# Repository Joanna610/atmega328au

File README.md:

# atmega328au

The project consist basic design of microcontroller avr atmega328.

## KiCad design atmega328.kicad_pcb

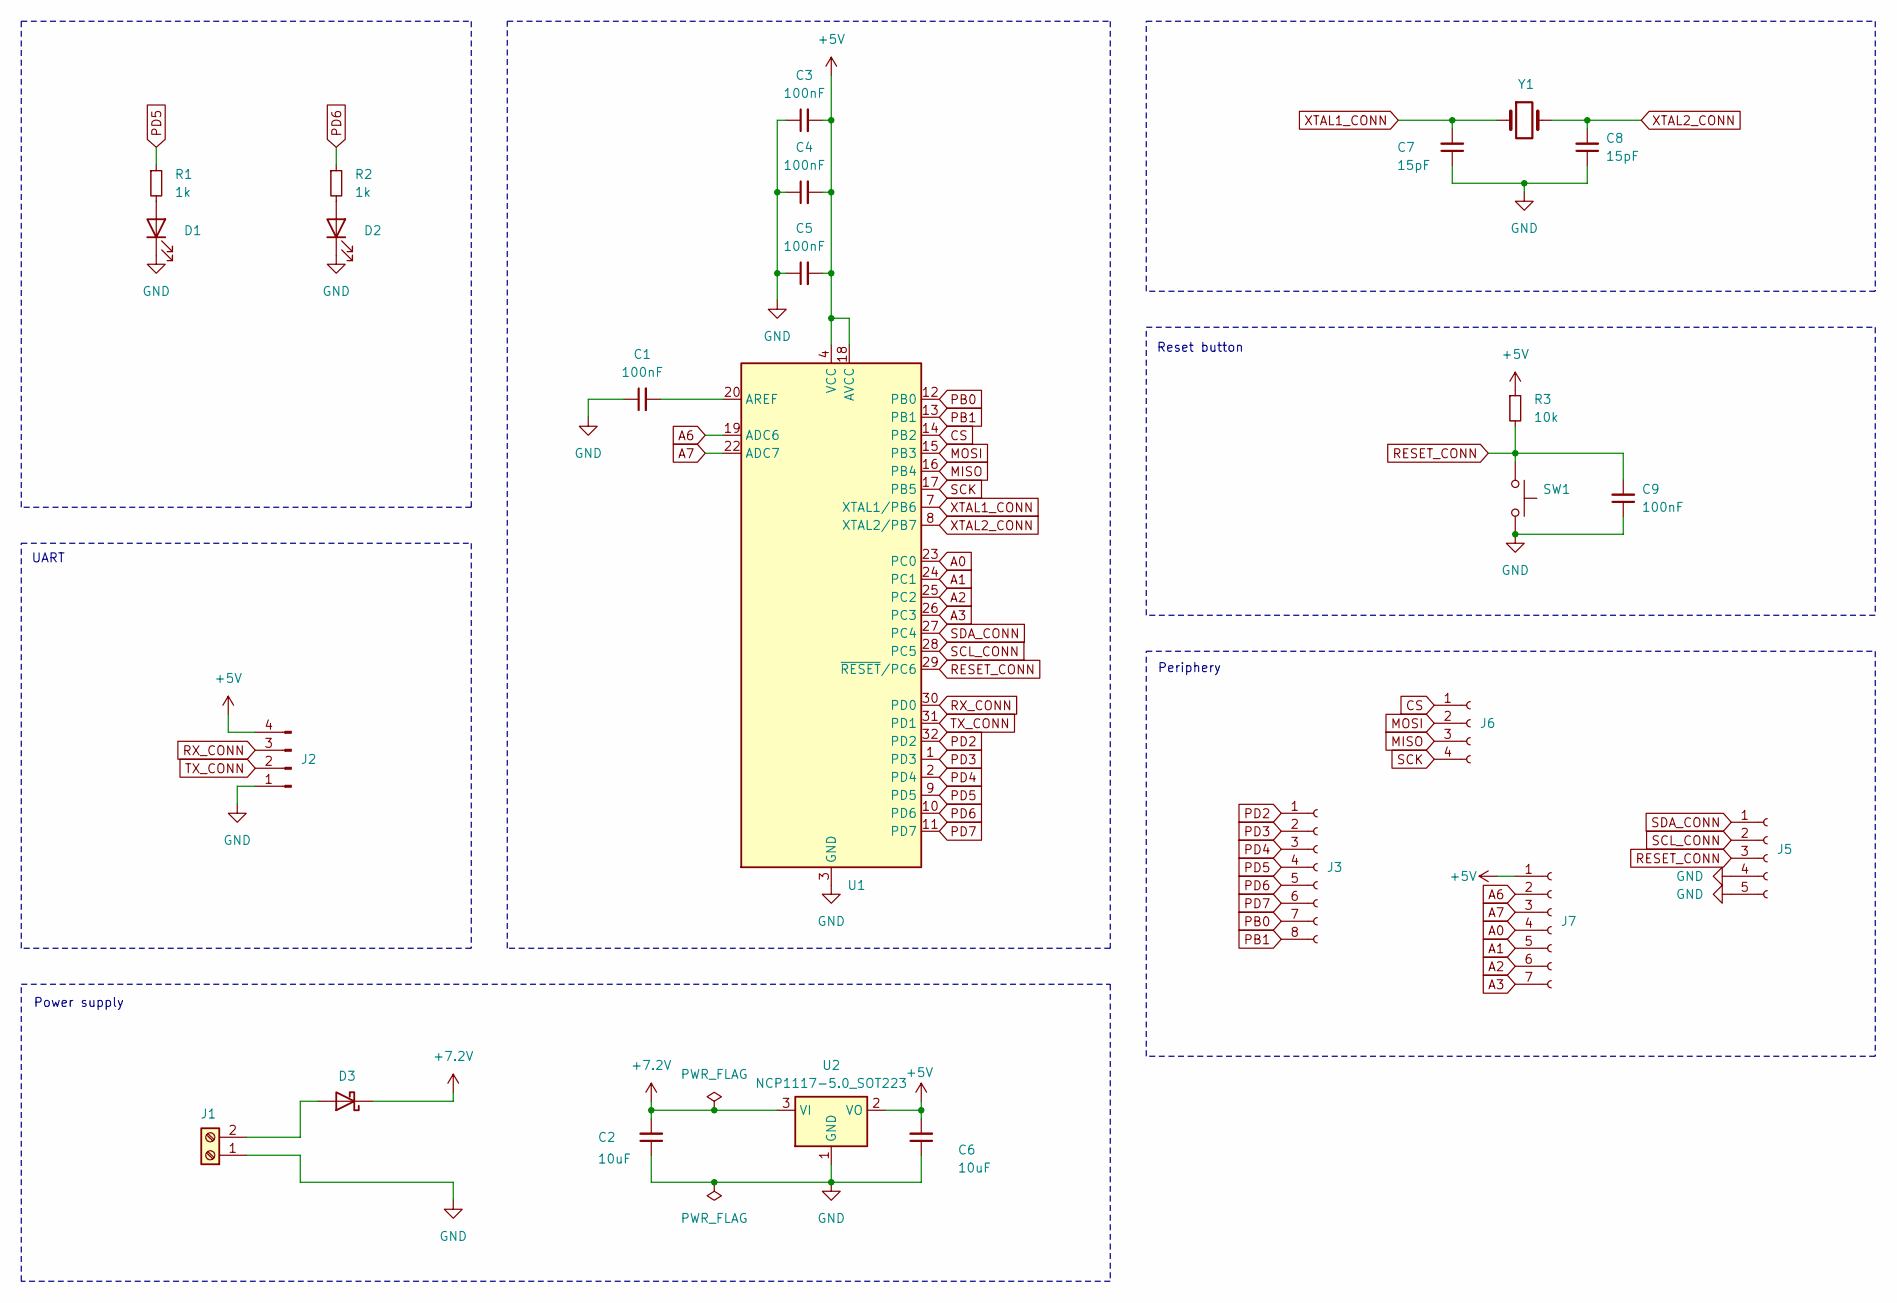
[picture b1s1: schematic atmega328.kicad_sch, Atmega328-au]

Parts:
C1, C3, C4, C5, C9: 100nF; C_0805_2012Metric_Pad1.18x1.45mm_HandSolder
C2, C6: 10uF; C_0805_2012Metric_Pad1.18x1.45mm_HandSolder
C7, C8: 15pF; C_0805_2012Metric_Pad1.18x1.45mm_HandSolder
D1, D2: LED; LED_1206_3216Metric_Pad1.42x1.75mm_HandSolder
D3: D_Schottky; R_Axial_DIN0207_L6.3mm_D2.5mm_P7.62mm_Horizontal
J1: input_supply; TE_826576-2_1x02_P3.96mm_Vertical
J2: UART; PinHeader_1x04_P2.54mm_Vertical
J3: Conn_01x08_Socket; PinSocket_1x08_P2.54mm_Vertical
J5: Conn_01x05_Socket; PinSocket_1x05_P2.54mm_Vertical
J6: Conn_01x04_Socket; PinSocket_1x04_P2.54mm_Vertical
J7: Conn_01x07_Socket; PinSocket_1x07_P2.54mm_Vertical
R1, R2: 1k; R_0805_2012Metric_Pad1.20x1.40mm_HandSolder
R3: 10k; R_0805_2012Metric_Pad1.20x1.40mm_HandSolder
SW1: SW_Push; SW_PUSH_1P1T_6x3.5mm_H5.0_APEM_MJTP1250
U1: ATmega328P-A; TQFP-32_7x7mm_P0.8mm
U2: NCP1117-5.0_SOT223; SOT-223-3_TabPin2
Y1: Crystal; Crystal_HC49-4H_Vertical

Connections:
+5V: C3.2, C4.2, C5.2, C6.2, J2.4, J7.1, R3.1, U1.4 (VCC), U1.6 (VCC), U1.18 (AVCC), U2.2 (VO)
+7.2V: C2.2, D3.1 (K), U2.3 (VI)
A0: J7.4, U1.23 (PC0)
A1: J7.5, U1.24 (PC1)
A2: J7.6, U1.25 (PC2)
A3: J7.7, U1.26 (PC3)
A6: J7.2, U1.19 (ADC6)
A7: J7.3, U1.22 (ADC7)
CS: J6.1, U1.14 (PB2)
GND: C1.1, C2.1, C3.1, C4.1, C5.1, C6.1, C7.1, C8.1, C9.1, D1.1 (K), D2.1 (K), J1.1, J2.1, J5.4, J5.5, SW1.2, U1.3 (GND), U1.5 (GND), U1.21 (GND), U2.1 (GND)
MISO: J6.3, U1.16 (PB4)
MOSI: J6.2, U1.15 (PB3)
unnamed: D1.2 (A), R1.2
unnamed: D2.2 (A), R2.2
unnamed: D3.2 (A), J1.2
unnamed: C1.2, U1.20 (AREF)
PB0: J3.7, U1.12 (PB0)
PB1: J3.8, U1.13 (PB1)
PD2: J3.1, U1.32 (PD2)
PD3: J3.2, U1.1 (PD3)
PD4: J3.3, U1.2 (PD4)
PD5: J3.4, R1.1, U1.9 (PD5)
PD6: J3.5, R2.1, U1.10 (PD6)
PD7: J3.6, U1.11 (PD7)
RESET_CONN: C9.2, J5.3, R3.2, SW1.1, U1.29 (~RESET/PC6)
RX_CONN: J2.3, U1.30 (PD0)
SCK: J6.4, U1.17 (PB5)
SCL_CONN: J5.2, U1.28 (PC5)
SDA_CONN: J5.1, U1.27 (PC4)
TX_CONN: J2.2, U1.31 (PD1)
XTAL1_CONN: C7.2, U1.7 (XTAL1/PB6), Y1.1
XTAL2_CONN: C8.2, U1.8 (XTAL2/PB7), Y1.2

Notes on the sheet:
Power supply
UART
Periphery
Reset button

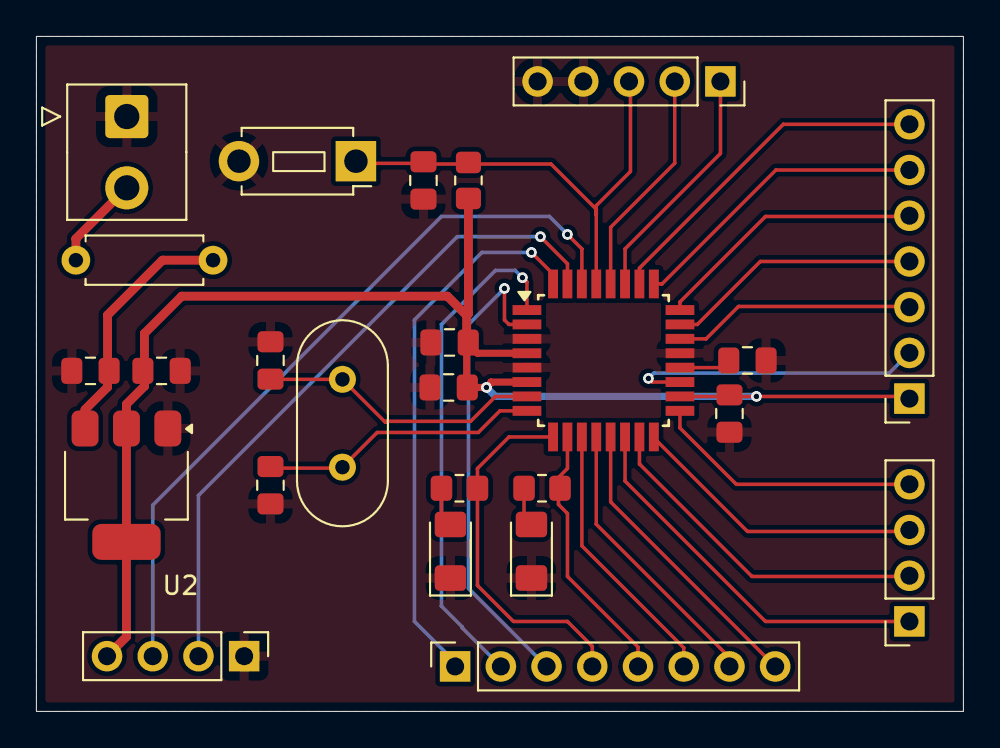
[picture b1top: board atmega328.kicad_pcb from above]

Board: 2 copper layers, 51.5 x 37.5 mm, 25 parts (0 on the bottom side), 32 nets.

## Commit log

2025-08-26 Adding final PCB design
